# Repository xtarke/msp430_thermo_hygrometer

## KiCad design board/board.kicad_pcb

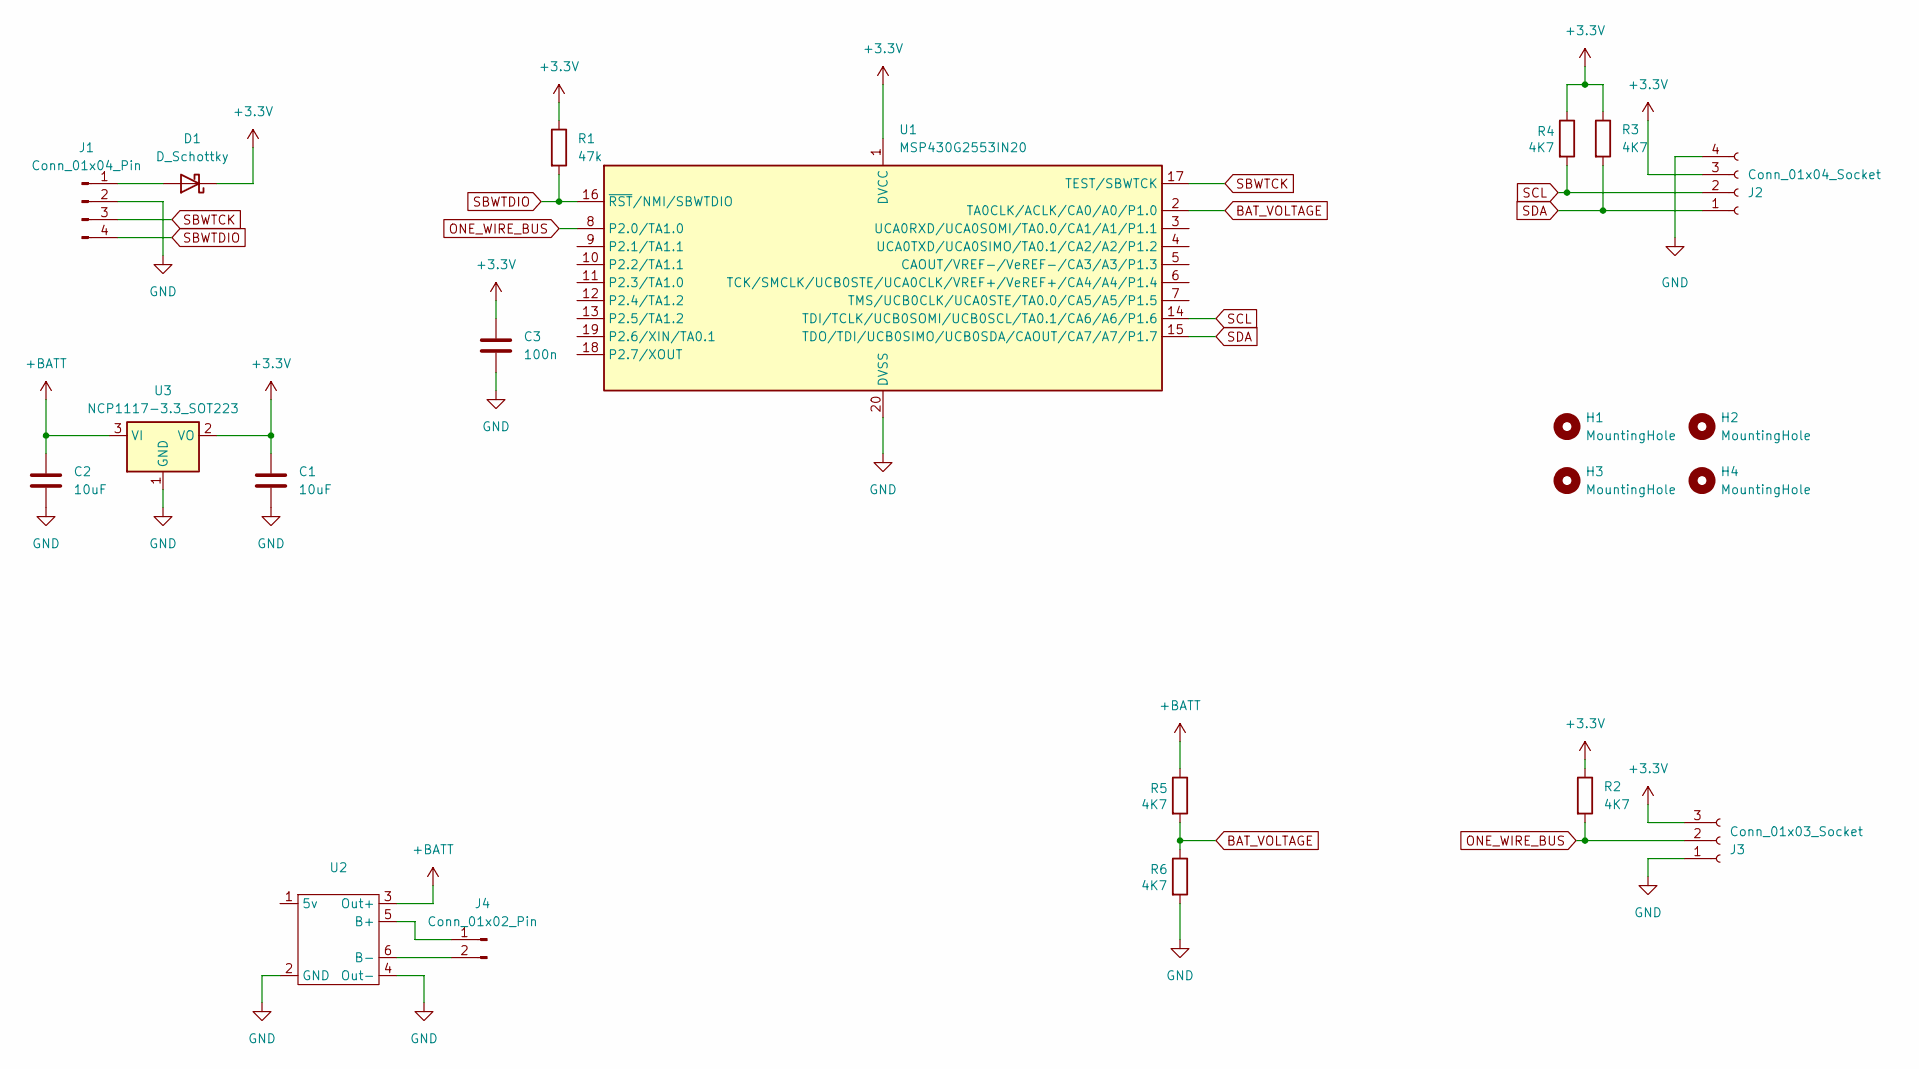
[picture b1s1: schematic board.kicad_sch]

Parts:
C1, C2: 10uF; C_0805_2012Metric
C3: 100n; C_0805_2012Metric
D1: D_Schottky; D_SMB
H1, H2, H3, H4: MountingHole; MountingHole_3.2mm_M3
J1: Conn_01x04_Pin; PinHeader_1x04_P2.54mm_Horizontal
J2: Conn_01x04_Socket; PinSocket_1x04_P2.54mm_Vertical
J3: Conn_01x03_Socket; PinSocket_1x03_P2.54mm_Horizontal
J4: Conn_01x02_Pin; PinHeader_1x02_P2.54mm_Horizontal
R1: 47k; R_0805_2012Metric_Pad1.20x1.40mm_HandSolder
R2, R3, R4, R5, R6: 4K7; R_0805_2012Metric_Pad1.20x1.40mm_HandSolder
U1: MSP430G2553IN20; DIP-20_W7.62mm
U2: TP4056-18650
U3: NCP1117-3.3_SOT223; SOT-223-3_TabPin2

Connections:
+3.3V: C1.1, C3.1, D1.1 (K), J2.3, J3.3, R1.1, R2.1, R3.1, R4.1, U1.1 (DVCC), U3.2 (VO)
+BATT: C2.1, R5.1, U2.3 (Out+), U3.3 (VI)
BAT_VOLTAGE: R5.2, R6.1, U1.2 (TA0CLK/ACLK/CA0/A0/P1.0)
GND: C1.2, C2.2, C3.2, J1.2, J2.4, J3.1, R6.2, U1.20 (DVSS), U2.2 (GND), U2.4 (Out-), U3.1 (GND)
unnamed: D1.2 (A), J1.1
unnamed: J4.1, U2.5 (B+)
unnamed: J4.2, U2.6 (B-)
ONE_WIRE_BUS: J3.2, R2.2, U1.8 (P2.0/TA1.0)
SBWTCK: J1.3, U1.17 (TEST/SBWTCK)
SBWTDIO: J1.4, R1.2, U1.16 (~RST/NMI/SBWTDIO)
SCL: J2.2, R4.2, U1.14 (TDI/TCLK/UCB0SOMI/UCB0SCL/TA0.1/CA6/A6/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)
SDA: J2.1, R3.2, U1.15 (TDO/TDI/UCB0SIMO/UCB0SDA/CAOUT/CA7/A7/P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)

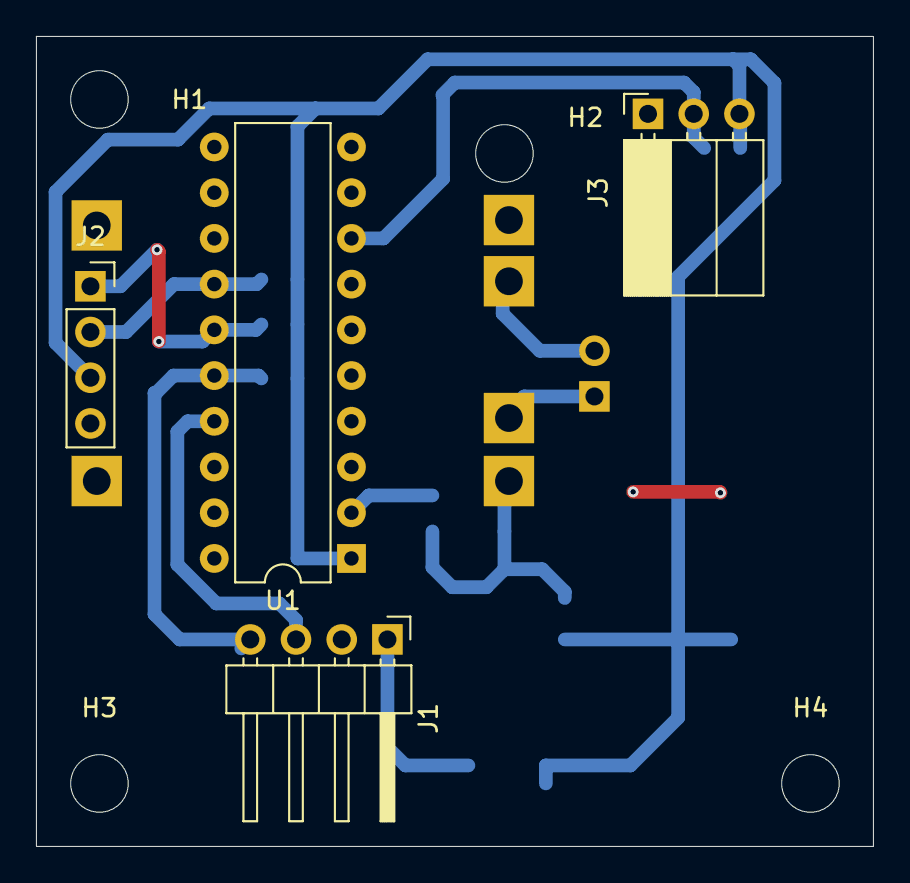
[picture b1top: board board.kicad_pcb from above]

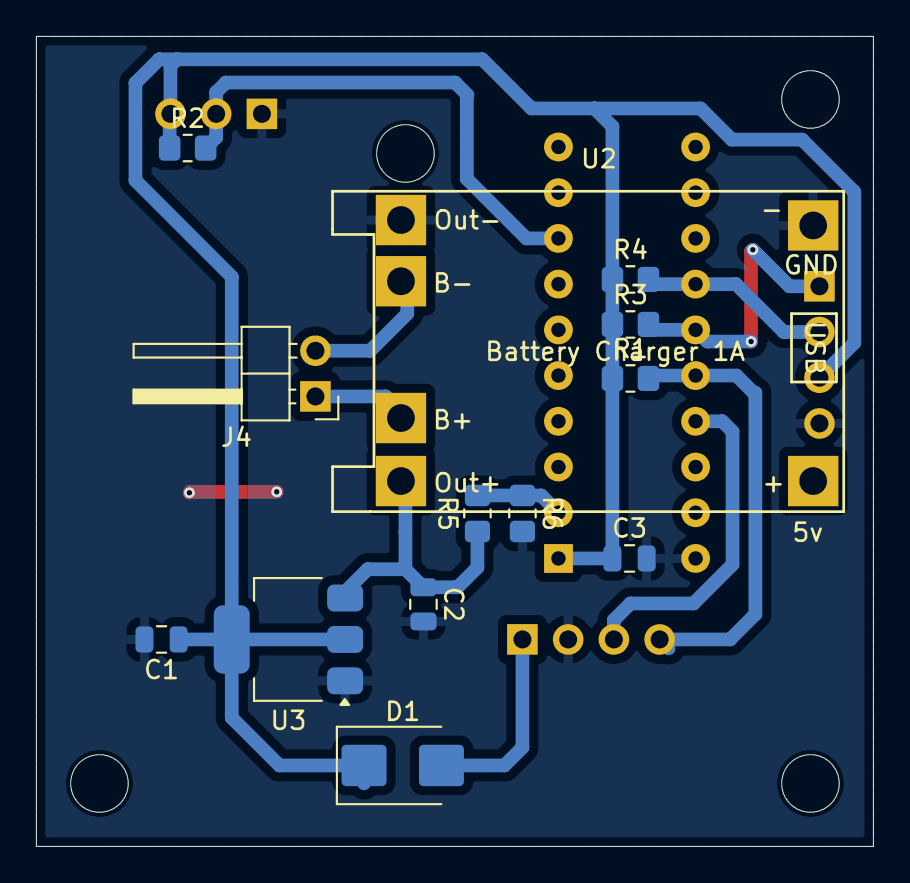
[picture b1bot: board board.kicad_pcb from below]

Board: 2 copper layers, 46.5 x 45.0 mm, 21 parts (13 on the bottom side), 12 nets.

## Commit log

2024-06-06 Initial files commit
2024-06-25 New repo organization. Upload CPP project
2024-06-27 Added battery info. Power on delay to wait for oled
2024-06-28 Added board
2024-06-28 Updated PCB to use turbocase
2024-07-02 Corrected sensor and oled pins
